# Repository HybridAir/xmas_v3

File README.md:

# xmas_v3
The successor to 2015's xmas_v2
http://xmasv3.hybridair.me/

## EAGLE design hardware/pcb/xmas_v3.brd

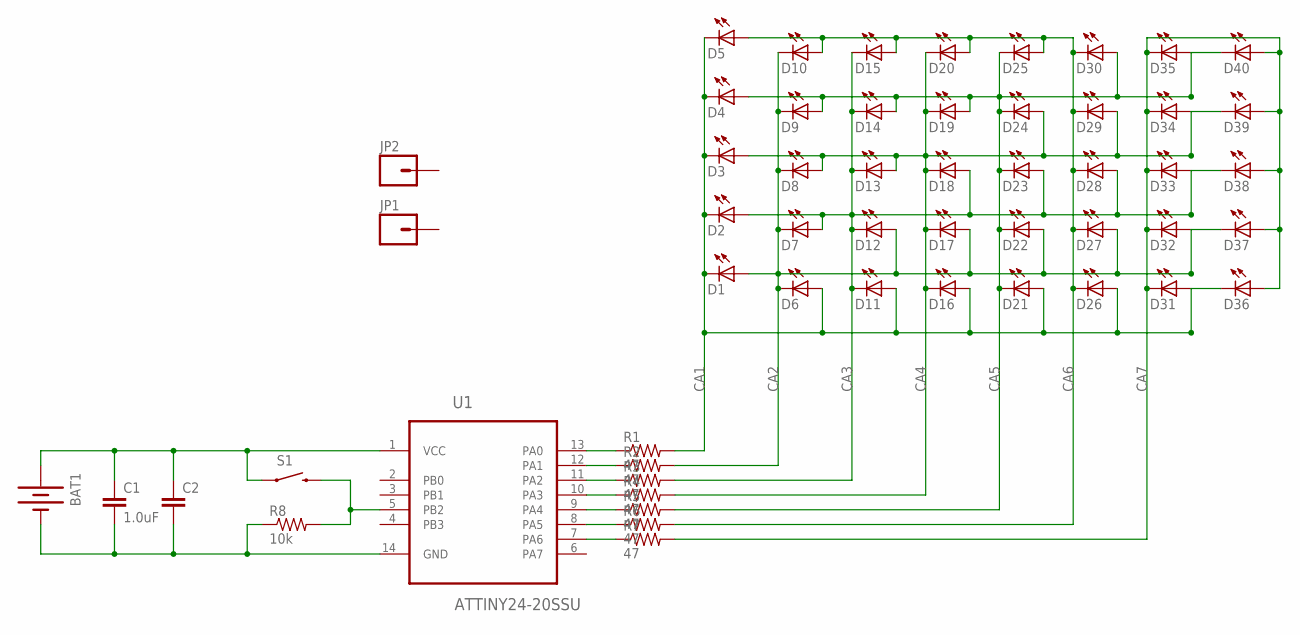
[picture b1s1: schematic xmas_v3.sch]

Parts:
BAT1: BATTERY20PTH; BATTCOM_20MM_PTH
C1: 1.0uF; 0805-CAP
C2: CAP0805; 0805
D1, D2, D3, D4, D5, D6, D7, D8, D9, D10, D11, D12, D13, D14, D15, D16, D17, D18, D19, D20, D21, D22, D23, D24, D25, D26, D27, D28, D29, D30, D31, D32, D33, D34, D35, D36, D37, D38, D39, D40: LEDCHIP-LED0603; CHIP-LED0603
JP1, JP2: M01PTH_NO_SILK_YES_STOP; 1X01_NO_SILK
R1, R2, R3, R4, R5, R6, R7: 47; R0603
R8: 10k; 0805
S1: SWITCH-MOMENTARY-2SMD-4; TACTILE_SWITCH_TALL
U1: ATTINY24-20SSU; SOIC127P600X175-14N

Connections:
CA1: D1.C, D2.C, D3.C, D4.C, D5.C, D6.A, D11.A, D16.A, D21.A, D26.A, D31.A, D36.C, R1.2
CA2: D1.A, D6.C, D7.C, D8.C, D9.C, D10.C, D12.A, D17.A, D22.A, D27.A, D32.A, D37.C, R2.2
CA3: D2.A, D7.A, D11.C, D12.C, D13.C, D14.C, D15.C, D18.A, D23.A, D28.A, D33.A, D38.C, R3.2
CA4: D3.A, D8.A, D13.A, D16.C, D17.C, D18.C, D19.C, D20.C, D24.A, D29.A, D34.A, D39.C, R4.2
CA5: D4.A, D9.A, D14.A, D19.A, D21.C, D22.C, D23.C, D24.C, D25.C, D30.A, D35.A, D40.C, R5.2
CA6: D5.A, D10.A, D15.A, D20.A, D25.A, D26.C, D27.C, D28.C, D29.C, D30.C, R6.2
CA7: D31.C, D32.C, D33.C, D34.C, D35.C, D36.A, D37.A, D38.A, D39.A, D40.A, R7.2
GND: BAT1.2 (-), C1.2, C2.2, R8.1, U1.14 (GND)
unnamed: BAT1.1 (+), C1.1, C2.1, S1.A2 (1), U1.1 (VCC)
unnamed: R8.2, S1.B2 (2), U1.5 (PB2)
unnamed: R1.1, U1.13 (PA0)
unnamed: R2.1, U1.12 (PA1)
unnamed: R3.1, U1.11 (PA2)
unnamed: R4.1, U1.10 (PA3)
unnamed: R5.1, U1.9 (PA4)
unnamed: R6.1, U1.8 (PA5)
unnamed: R7.1, U1.7 (PA6)

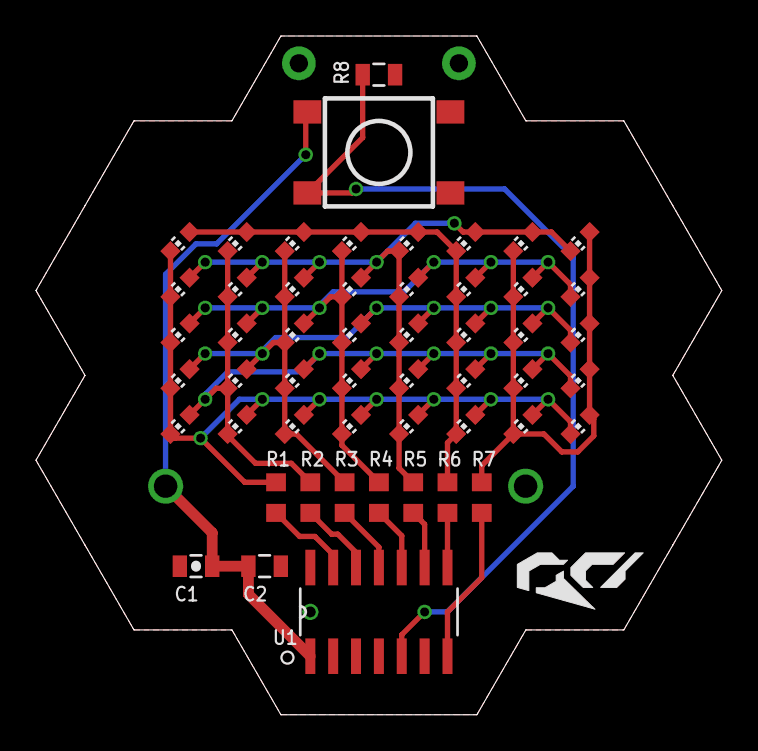
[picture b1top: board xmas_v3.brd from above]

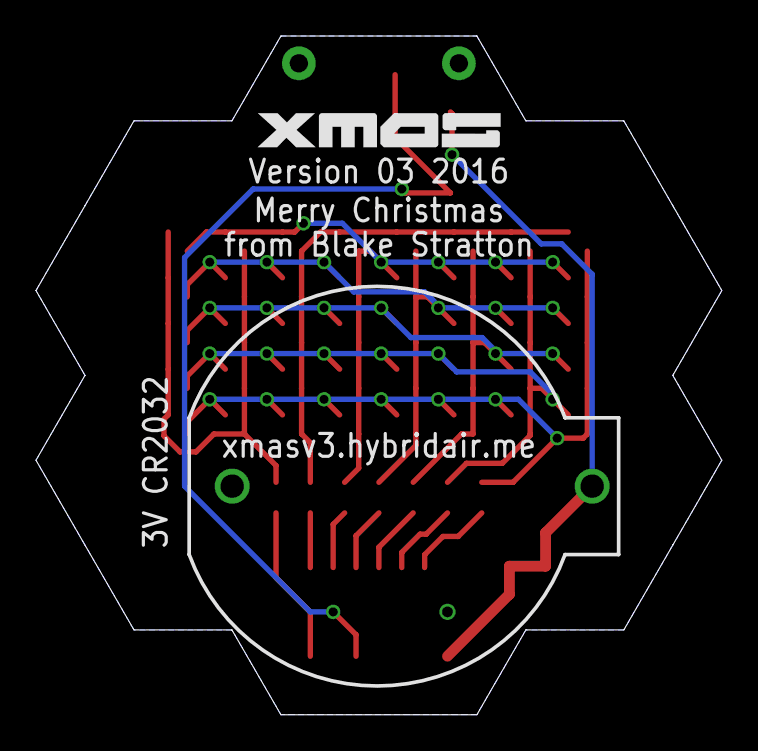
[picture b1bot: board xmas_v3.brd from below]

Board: 2 copper layers, 38.1 x 37.7 mm, 57 parts (2 on the bottom side), 17 nets.

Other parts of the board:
U$1: AR1
U$2: XMAS

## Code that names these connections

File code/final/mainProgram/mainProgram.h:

#ifndef _MAINPROGRAM_h_
#define _MAINPROGRAM_h_

//MAIN
#define BUTTON              PB2
#define ANIM_DELAY			25						//min ms the button needs to be held to change animations
#define SLEEP_DELAY			1000					//min ms the button needs to be held to enable sleep mode
#define SLEEPTIME			3600000					//time in ms to wait until auto sleeping (1 hour, 4 minutes slow)
//#define SLEEPTIME			30000					//time in ms to wait until auto sleeping (1 hour, 4 minutes slow)

#define F_CPU 8000000UL


//DISPLAY
//display section names with their cooresponding charpliex pins
//F isn't used becuase AVR uses it for frequency stuff
/* #define A PA0
#define B PA1
#define C PA2
#define D PA3
#define E PA4
#define G PA5
#define H PA6 */
#define H PA0
#define G PA1
#define E PA2
#define D PA3
#define C PA4
#define B PA5
#define A PA6

//total number of leds in the display
#define NUM_LEDS 40

#define DISPLAY_WIDTH  8
#define DISPLAY_HEIGHT 5

#define NUM_SECTIONS 7
#define PREOFFSET 3


//ANIM
#define MAP_START      47

#define CHAR_WIDTH 5

#define TOTAL_STRINGS 5           
#define STRINGLENGTH 18          //largest string is 18 bytes long, so they all need to be

#define TEXTSPEED 100
#define FIRSTDELAY  1000

#endif

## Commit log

2016-10-23 :space_invader: Added .gitattributes & .gitignore files
2016-10-23 Initial creation
2016-10-23 Moved things around for better organization
2016-10-23 my compiler doesn't like the word main by itself
2016-10-23 Moved defines to their own header file
2016-10-23 Added character map writing and reading
2016-10-23 Cleanup
2016-10-23 Added all character maps
2016-10-23 Init
2016-10-23 Moved relevant code to anim.ino
2016-10-23 Rename
2016-10-23 Cleanup before I break everything
2016-10-24 it compiles
    but doesn't work
2016-10-24 what the fuck have I done
    it still compiles
2016-10-25 Trying a slightly different approach
    since what I was doing before is turning into a giant clusterfuck
2016-10-27 fuck this shit nothing is working
2016-11-02 Reverting back to the last working code
2016-11-04 Got basic led display working on the attiny
2016-11-04 Cleanup before I start optimizing
    it works perfectly fine right now so this is a good fallback position
2016-11-04 Changed ledGrid to use progmem
    Got a fuckload of ram and storage back, works
2016-11-04 Made more optimizations to the display code
    Displays each whole section at once instead of a single led at a time,
    result is a brighter display but more program space, works
2016-11-04 Saved 30 bytes and some ram
    still works
2016-11-04 Forgot some cleanup
2016-11-04 Got very basic character display working
    still works
2016-11-04 Added offset character display
    works
2016-11-04 Added all character maps and character oriented display
    works
2016-11-04 Reorganization and init
    still works
2016-11-05 Static string display is working
    not sure how but it does??????
2016-11-06 Fixed character spacing
    works
2016-11-06 Barely got animation working
    it doesn't work right but it does something so, going to change a bunch
    of stuff now, but this is a decent reference point
2016-11-06 It's great when you don't remember what your own code did and you didn't comment it for some fuCKING REASON
2016-11-06 I fixed the spacing problem, now I can get back on with my life
2016-11-07 Got multiple saved strings working
    works
2016-11-07 Cleanup and optimizations
    still works
2016-11-07 Got button string switching working
    works
2016-11-07 Fixed some character maps
2016-11-07 Made some tiny optimizations
2016-11-07 I added button detection code but millis() or something has decided to fuck with me
    why is this not working, like it compiles but
2016-11-08 Why the fuck is this working now I literally just copied the concept I was using before
2016-11-08 Got button holding working
    works
2016-11-08 Got sleep working
    jesus christ this was the only code that easily transferred over without
    fucking me around
2016-11-08 Added sleep timer
2016-11-08 Fixed the sleep timer
    works now, wouldn't immediately go to sleep after waking up
2016-11-08 Removed unecessary character maps
    saved 60 bytes
2016-11-08 Saved another 56 bytes
    works
2016-11-08 Got it down to 2038 bytes compiled
    All done programming now (unless any new bugs appear), this should fit
    on an attiny24 now
2016-11-08 oops
2016-11-08 Changed some character maps
2016-11-09 Moved test code
2016-11-11 Changed display pinout to make pcb design easier
2016-11-11 All parts added
2016-11-11 Ready for PCB design
2016-11-12 test
2016-11-12 Finished PCB design
2016-11-12 More cleanup
2016-11-12 Final minor changes
2016-11-12 oops I forgot this

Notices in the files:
parts and their libraries:
SparkFun-Electromechanical: Licensing: Creative Commons ShareAlike 4.0 International - https://creativecommons.org/licenses/by-sa/4.0
